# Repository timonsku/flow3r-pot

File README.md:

# flow3r-pot

A tool that gives access to a UART port on USB-C SBU pins.
It combines a USB to UART IC and a USB hub to connect both the USB port of the device and the UART itself to the connected USB Host.

The design can be ordered at JLCPCB Assembly service with the included gerber, bom and cpl file.

You can change the IO voltage by placing your own reference voltage LDO on the LDL1117 footprint and cut and re-solder JP1. By default the 3v3 reference is supplied by the CH343P.

The extra IOs from the CH343P are broken out to pin headers. This can be useful if you plan on using this board with other hardware.

While this was developed for the flow3r badge there is nothing inherently specific to that hardware. You can design you own board that places UART on the two SBU pins of your USB-C connector and use this as a debugger for that hardware as well.

Or modify it and put SWD on those pins instead. None of this is USB-C compliant but there is also fairly little to no risk of damaging anything if you were to plug this into a normal device but proceed at your own risk of course. The SBU pins are usually used for either digital audio or analog audio so devices usually will expect voltages up to 3v3 on those pins.

You can also do spicy things like supply an external VBUS via the pin headers.

The 2x USB-A connectors just break out the available extra ports on the USB hub. They are completely optional and are standard USB ports, nothing special about them. Purely for convenience and because we can (and its very cheap).

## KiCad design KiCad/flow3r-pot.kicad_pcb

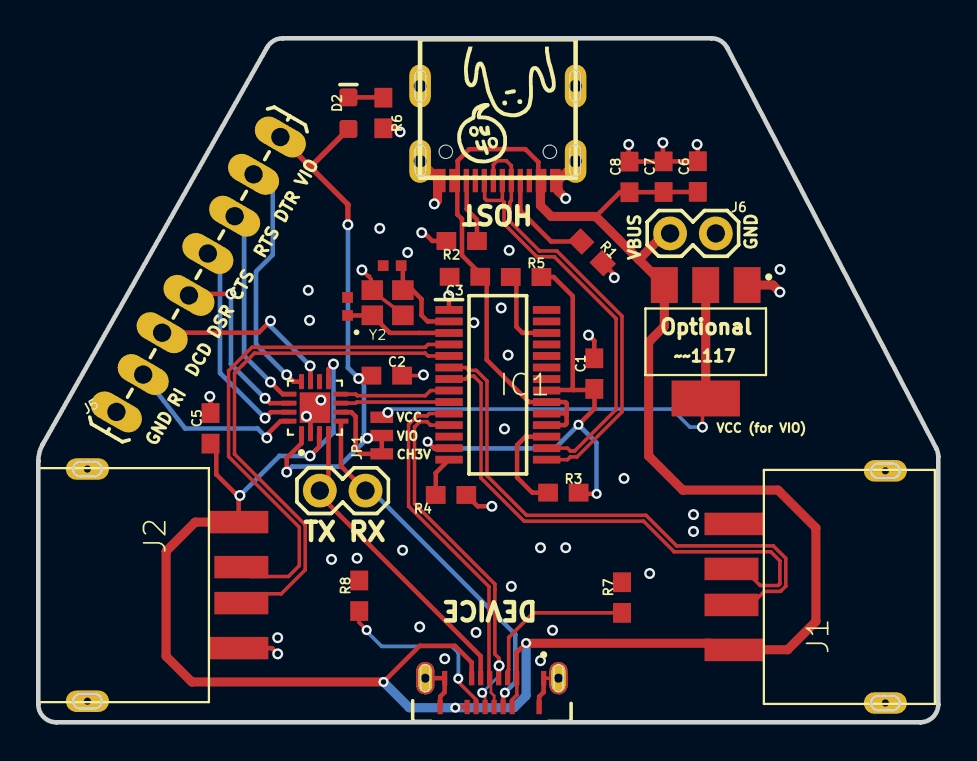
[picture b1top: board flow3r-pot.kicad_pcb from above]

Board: 2 copper layers, 50.0 x 38.0 mm, 31 parts (0 on the bottom side), 34 nets.

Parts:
C1, C2, C3, C5, C6, C7, C8: 10uF; 0603
D2: RED; LED-0603
DNP-C4, DNP-C9: 20pF; 0402-TIGHT
IC1: FE1.1S-BSOP28BCN; SOP64P600X175-28N
J1, J2: JE-USB-A-C42595
J3: TYPE-C-31-G-08-2.0-ONLY
J4, J6: 1X02
J5: 1X08_LOCK_LONGPADS
JP1: JUMPER-SMT_3_1-NC_TRACE_NO-SILK; SMT-JUMPER_3_1-NC_TRACE_NO-SILK
R1, R2, R7, R8: 5.1k; 0603
R3, R5, R6: 10k; 0603
R4: 2.7k; 0603
U1: CH343P; QFN50P300X300X80-17N
U2: LDL1117S12R; SOT230P700X180-4N
U$2: OHNO-6.5
USB-C-HOST0: C709357; USB-TYPE-C_16PIN-MALE-TYPE-C-31-M-12
Y2: 12MHZ; CRYSTAL-SMD-2X2.5MM

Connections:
CH_3V3: JP1.3, U1.6
CTS: J5.5, U1.15
D1_N: IC1.10, J3.A7, J3.B7
D1_P: IC1.11, J3.A6, J3.B6
D2_N: IC1.8, U1.8
D2_P: IC1.9, U1.7
D3_N: IC1.6, J1.D-
D3_P: IC1.7, J1.D+
D4_N: IC1.4, J2.D-
D4_P: IC1.5, J2.D+
DCD: J5.3, U1.11
DSR: J5.4, U1.14
DTR: J5.7, U1.12
DU_N: IC1.15, USB-C-HOST0.A7, USB-C-HOST0.B7
DU_P: IC1.16, USB-C-HOST0.A6, USB-C-HOST0.B6
GND: C1.2, C2.2, C3.2, C5.2, C6.2, C7.2, C8.2, DNP-C4.2, DNP-C9.2, IC1.1, J1.GND, J1.SHIELD-1, J1.SHIELD-2, J2.GND, J2.SHIELD-1, J2.SHIELD-2, J3.A1, J3.A12, J3.B1, J3.B12, J3.S1, J3.S2, J5.1, J6.2, R1.2, R2.2, R4.1, R6.2, R7.2, R8.2, U1.2, U1.17, U2.1, USB-C-HOST0.0, USB-C-HOST0.0-1, USB-C-HOST0.0-2, USB-C-HOST0.0-3, USB-C-HOST0.A1, USB-C-HOST0.A12, USB-C-HOST0.B1, USB-C-HOST0.B12
unnamed: R2.1, USB-C-HOST0.B5
unnamed: R1.1, USB-C-HOST0.A5
unnamed: D2.C, R6.1
unnamed: J3.B5, R8.1
unnamed: J3.A5, R7.1
OVCJ: IC1.26, R5.1
REXT: IC1.14, R4.2
RI: J5.2, U1.16
RTS: J5.6, U1.13
RXD: J3.B8, J4.1, U1.5
TXD: J3.A8, J4.2, U1.4
VBUS: C3.1, C5.1, C6.1, C7.1, C8.1, IC1.18, IC1.19, IC1.20, J1.VBUS, J2.VBUS, J3.A4, J3.A9, J3.B4, J3.B9, J6.1, U1.3, U1.9, U2.3, USB-C-HOST0.A4, USB-C-HOST0.A9, USB-C-HOST0.B4, USB-C-HOST0.B9
VCC: JP1.1, U2.2, U2.4
VD33: C1.1, IC1.13, IC1.21, R3.2, R5.2
VIO: C2.1, D2.A, J5.8, JP1.2, U1.1
XIN: DNP-C4.1, IC1.3, Y2.P1
XOUT: DNP-C9.1, IC1.2, Y2.P3
XRSTJ: IC1.17, R3.1

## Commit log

2023-12-27 add KiCad imports
2023-12-27 add license
2023-12-27 Add image
